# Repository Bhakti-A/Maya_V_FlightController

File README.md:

# Maya_V Flight Controller

This is a custom flight controller PCB designed for drones.

## PCB Preview

## Features

- **Microcontroller:** STM32F405  
- **IMU Sensor:** ICM-20948  
- **Barometer:** BMP280  
- **Video OSD:** MAX7456 
- **ESC Outputs:** 4× PWM channels (with extra PWM expansion)  
- **Communication Interfaces:** UART, I2C, USB  

## Hardware Design

### Schematic & PCB Layout

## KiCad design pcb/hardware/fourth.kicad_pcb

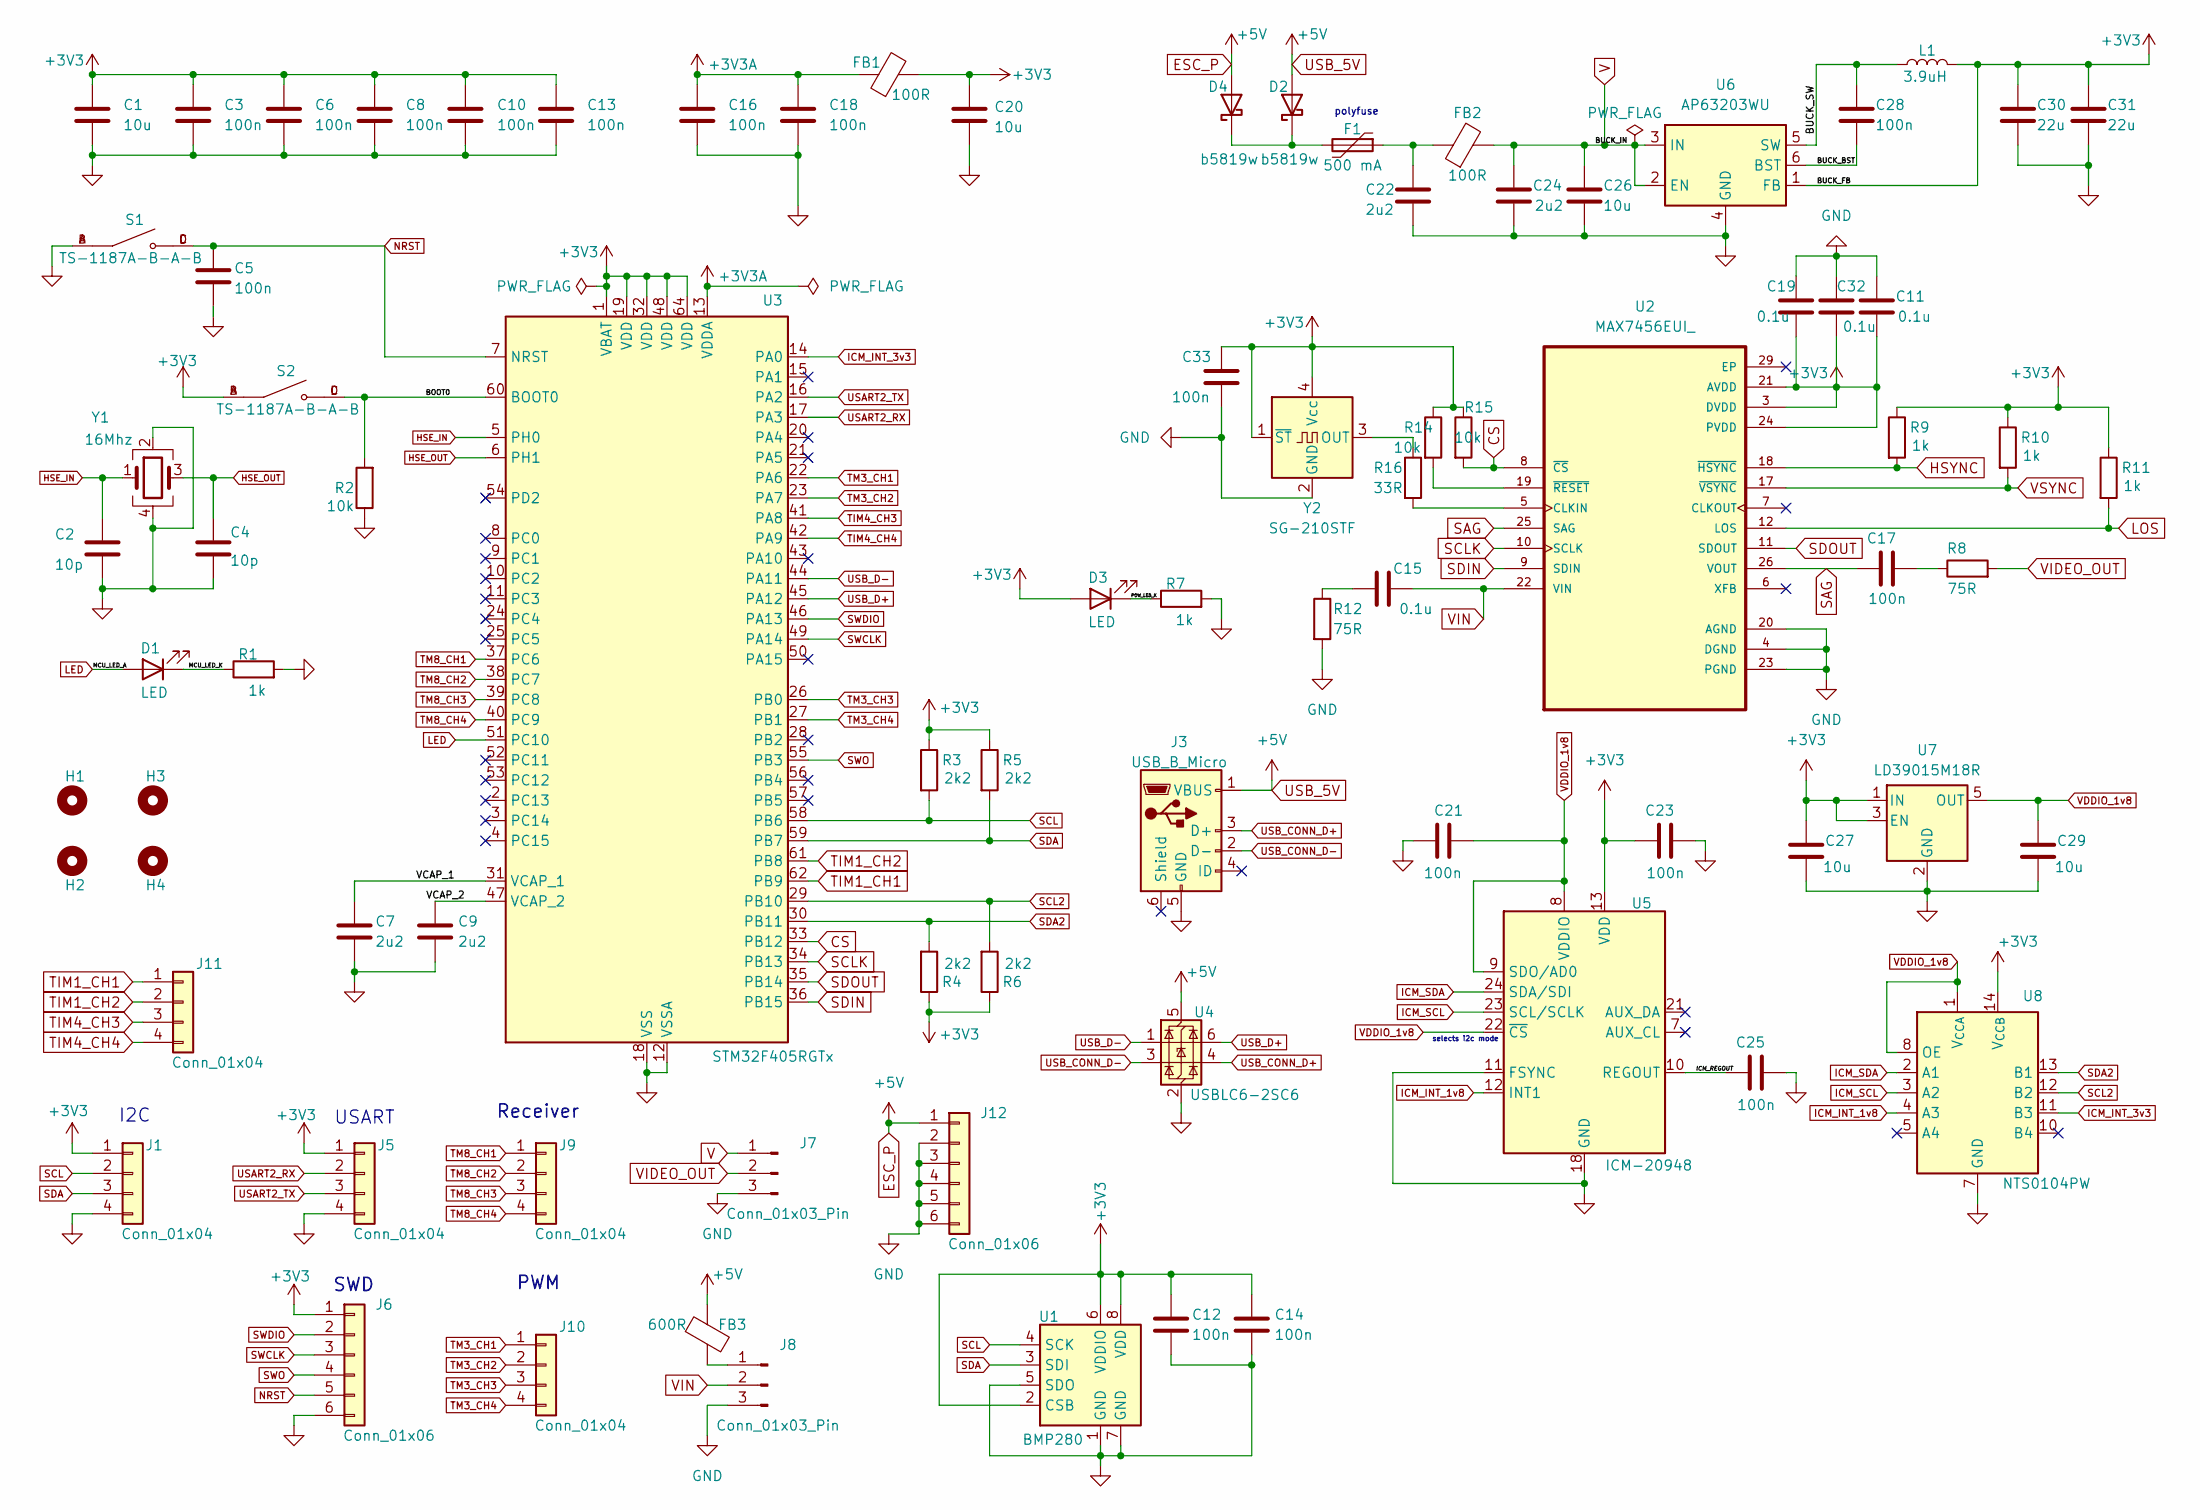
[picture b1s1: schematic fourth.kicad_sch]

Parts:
C1, C20, C26, C27, C29: 10u; C_0805_2012Metric
C2, C4: 10p; C_0402_1005Metric
C3, C5, C6, C8, C10, C12, C13, C14, C16, C18, C21, C23, C25, C28, C33: 100n; C_0402_1005Metric
C7, C9, C22, C24: 2u2; C_0603_1608Metric
C11, C19, C32: 0.1u; C_0402_1005Metric
C15: 0.1u; C_0603_1608Metric
C17: 100n; C_0603_1608Metric
C30, C31: 22u; C_0805_2012Metric
D1, D3: LED; LED_0603_1608Metric
D2, D4: b5819w; D_SOD-123
F1: 500 mA; Fuse_0603_1608Metric
FB1, FB2: 100R; L_0805_2012Metric
FB3: 600R; L_0805_2012Metric
H1, H2, H3, H4: MountingHole; MountingHole_3.2mm_M3_Pad_Via
J1, J5, J9, J10, J11: Conn_01x04; JST_ZH_B4B-ZR_1x04_P1.50mm_Vertical
J3: USB_B_Micro; USB_Micro-B_Amphenol_10118193-0001LF_Horizontal
J6, J12: Conn_01x06; JST_ZH_B6B-ZR_1x06_P1.50mm_Vertical
J7, J8: Conn_01x03_Pin; JST_ZH_B3B-ZR_1x03_P1.50mm_Vertical
L1: 3.9uH; L_Sunlord_SWPA4030S
R1, R7, R9, R10, R11: 1k; R_0603_1608Metric
R2, R14, R15: 10k; R_0603_1608Metric
R3, R4, R5, R6: 2k2; R_0603_1608Metric
R8, R12: 75R; R_0603_1608Metric
R16: 33R; R_0603_1608Metric
S1, S2: TS-1187A-B-A-B; SW_TS-1187A-B-A-B; PARTREV A0
U1: BMP280; Bosch_LGA-8_2x2.5mm_P0.65mm_ClockwisePinNumbering
U2: MAX7456EUI_; SOP65P637X110-28N
U3: STM32F405RGTx; LQFP-64_10x10mm_P0.5mm
U4: USBLC6-2SC6; SOT-23-6
U5: ICM-20948; InvenSense_QFN-24_3x3mm_P0.4mm
U6: AP63203WU; TSOT-23-6
U7: LD39015M18R; SOT-23-5
U8: NTS0104PW; TSSOP-14_4.4x5mm_P0.65mm
Y1: 16Mhz; Crystal_SMD_3225-4Pin_3.2x2.5mm
Y2: SG-210STF; Oscillator_SMD_SeikoEpson_SG210-4Pin_2.5x2.0mm

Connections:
+3V3: C1.1, C3.1, C6.1, C8.1, C10.1, C11.2, C12.1, C13.1, C14.2, C19.2, C20.1, C23.1, C27.1, C30.1, C31.1, C32.1, C33.1, D3.2 (A), FB1.2, J1.1, J5.1, J6.1, L1.2, R3.1, R4.1, R5.1, R6.1, R9.1, R10.1, R11.1, R14.1, R15.1, S2.A, S2.B, U1.2 (CSB), U1.6 (VDDIO), U1.8 (VDD), U2.3 (DVDD), U2.21 (AVDD), U2.24 (PVDD), U3.1 (VBAT), U3.19 (VDD), U3.32 (VDD), U3.48 (VDD), U3.64 (VDD), U5.13 (VDD), U6.1 (FB), U7.1 (IN), U7.3 (EN), U8.14 (V_{CCB}), Y2.1 (~ST), Y2.4 (Vcc)
+3V3A: C16.1, C18.1, FB1.1, U3.13 (VDDA)
/BOOT0: R2.2, S2.C, S2.D, U3.60 (BOOT0)
/BUCK_BST: C28.2, U6.6 (BST)
/BUCK_SW: C28.1, L1.1, U6.5 (SW)
/ICM_REGOUT: C25.1, U5.10 (REGOUT)
/MCU_LED_K: D1.1 (K), R1.1
/POW_LED_K: D3.1 (K), R7.1
/VCAP_1: C7.1, U3.31 (VCAP_1)
/VCAP_2: C9.1, U3.47 (VCAP_2)
CS: R15.2, U2.8 (~CS), U3.33 (PB12)
ESC_P: D2.2 (A), D4.2 (A), FB3.1, J3.1 (VBUS), J12.1, U4.5 (VBUS)
GND: C1.2, C2.2, C3.2, C4.2, C5.2, C6.2, C7.2, C8.2, C9.2, C10.2, C11.1, C12.2, C13.2, C14.1, C16.2, C18.2, C19.1, C20.2, C21.2, C22.2, C23.2, C24.2, C25.2, C26.2, C27.2, C29.2, C30.2, C31.2, C32.2, C33.2, J1.4, J3.5 (GND), J5.4, J6.6, J7.3, J8.3, J12.2, J12.3, J12.4, J12.5, J12.6, R1.2, R2.1, R7.2, R12.2, S1.A, S1.B, U1.1 (GND), U1.5 (SDO), U1.7 (GND), U2.4 (DGND), U2.20 (AGND), U2.23 (PGND), U3.12 (VSSA), U3.18 (VSS), U3.63 (VSS), U4.2 (GND), U5.11 (FSYNC), U5.18 (GND), U5.20 (GND), U6.4 (GND), U7.2 (GND), U8.7 (GND), Y1.2, Y1.4, Y2.2 (GND)
HSE_IN: C2.1, U3.5 (PH0), Y1.1
HSE_OUT: C4.1, U3.6 (PH1), Y1.3
HSYNC: R9.2, U2.18 (~HSYNC)
ICM_INT_1v8: U5.12 (INT1), U8.4 (A3)
ICM_INT_3v3: U3.14 (PA0), U8.11 (B3)
ICM_SCL: U5.23 (SCL/SCLK), U8.3 (A2)
ICM_SDA: U5.24 (SDA/SDI), U8.2 (A1)
LED: D1.2 (A), U3.51 (PC10)
LOS: R11.2, U2.12 (LOS)
NRST: C5.1, J6.5, S1.C, S1.D, U3.7 (NRST)
unnamed: C15.1, R12.1
unnamed: C17.2, R8.1
unnamed: D2.1 (K), D4.1 (K), F1.2
unnamed: FB3.2, J8.1
unnamed: R16.2, U2.5 (CLKIN)
unnamed: R14.2, U2.19 (~RESET)
unnamed: R16.1, Y2.3 (OUT)
SAG: C17.1, U2.25 (SAG), U2.26 (VOUT)
SCL: J1.2, R3.2, U1.4 (SCK), U3.58 (PB6)
SCL2: R6.2, U3.29 (PB10), U8.12 (B2)
SCLK: U2.10 (SCLK), U3.34 (PB13)
SDA: J1.3, R5.2, U1.3 (SDI), U3.59 (PB7)
SDA2: R4.2, U3.30 (PB11), U8.13 (B1)
SDIN: U2.9 (SDIN), U3.36 (PB15)
SDOUT: U2.11 (SDOUT), U3.35 (PB14)
SWCLK: J6.3, U3.49 (PA14)
SWDIO: J6.2, U3.46 (PA13)
SWO: J6.4, U3.55 (PB3)
TIM1_CH1: J11.1, U3.62 (PB9)
TIM1_CH2: J11.2, U3.61 (PB8)
TIM4_CH3: J11.3, U3.41 (PA8)
TIM4_CH4: J11.4, U3.42 (PA9)
TM3_CH1: J10.1, U3.22 (PA6)
TM3_CH2: J10.2, U3.23 (PA7)
TM3_CH3: J10.3, U3.26 (PB0)
TM3_CH4: J10.4, U3.27 (PB1)
TM8_CH1: J9.1, U3.37 (PC6)
TM8_CH2: J9.2, U3.38 (PC7)
TM8_CH3: J9.3, U3.39 (PC8)
TM8_CH4: J9.4, U3.40 (PC9)
USART2_RX: J5.2, U3.17 (PA3)
USART2_TX: J5.3, U3.16 (PA2)
USB_CONN_D+: J3.3 (D+), U4.4 (I/O2)
USB_CONN_D-: J3.2 (D-), U4.3 (I/O2)
USB_D+: U3.45 (PA12), U4.6 (I/O1)
USB_D-: U3.44 (PA11), U4.1 (I/O1)
VDDIO_1v8: C21.1, C29.1, U5.8 (VDDIO), U5.9 (SDO/AD0), U5.22 (~CS), U7.5 (OUT), U8.1 (V_{CCA}), U8.8 (OE)
VIDEO_OUT: J7.2, R8.2
VIN: C15.2, J8.2, U2.22 (VIN)
VSYNC: R10.2, U2.17 (~VSYNC)

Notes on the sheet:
PWM
SWD
selects i2c mode
USART
polyfuse
Receiver
I2C

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
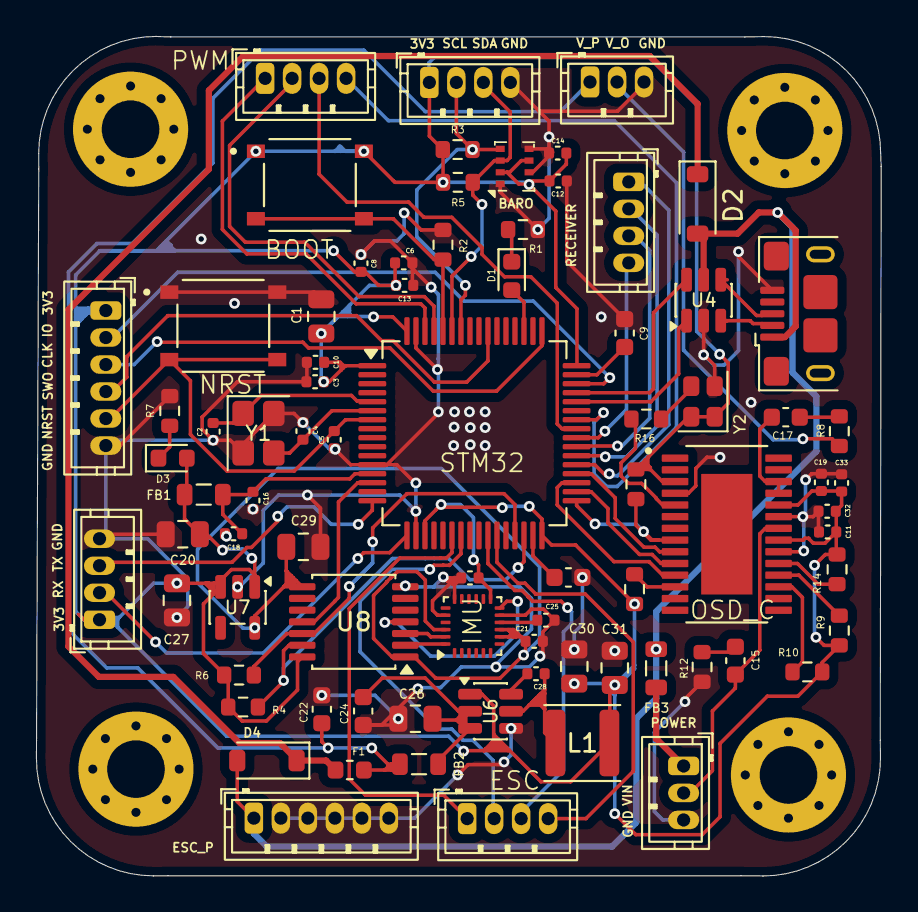
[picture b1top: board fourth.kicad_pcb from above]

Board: 2 copper layers, 46.9 x 46.6 mm, 83 parts (0 on the bottom side), 65 nets.

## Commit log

2026-01-23 PCB files and README
2026-01-23 readme added
2026-02-01 Update pcb
